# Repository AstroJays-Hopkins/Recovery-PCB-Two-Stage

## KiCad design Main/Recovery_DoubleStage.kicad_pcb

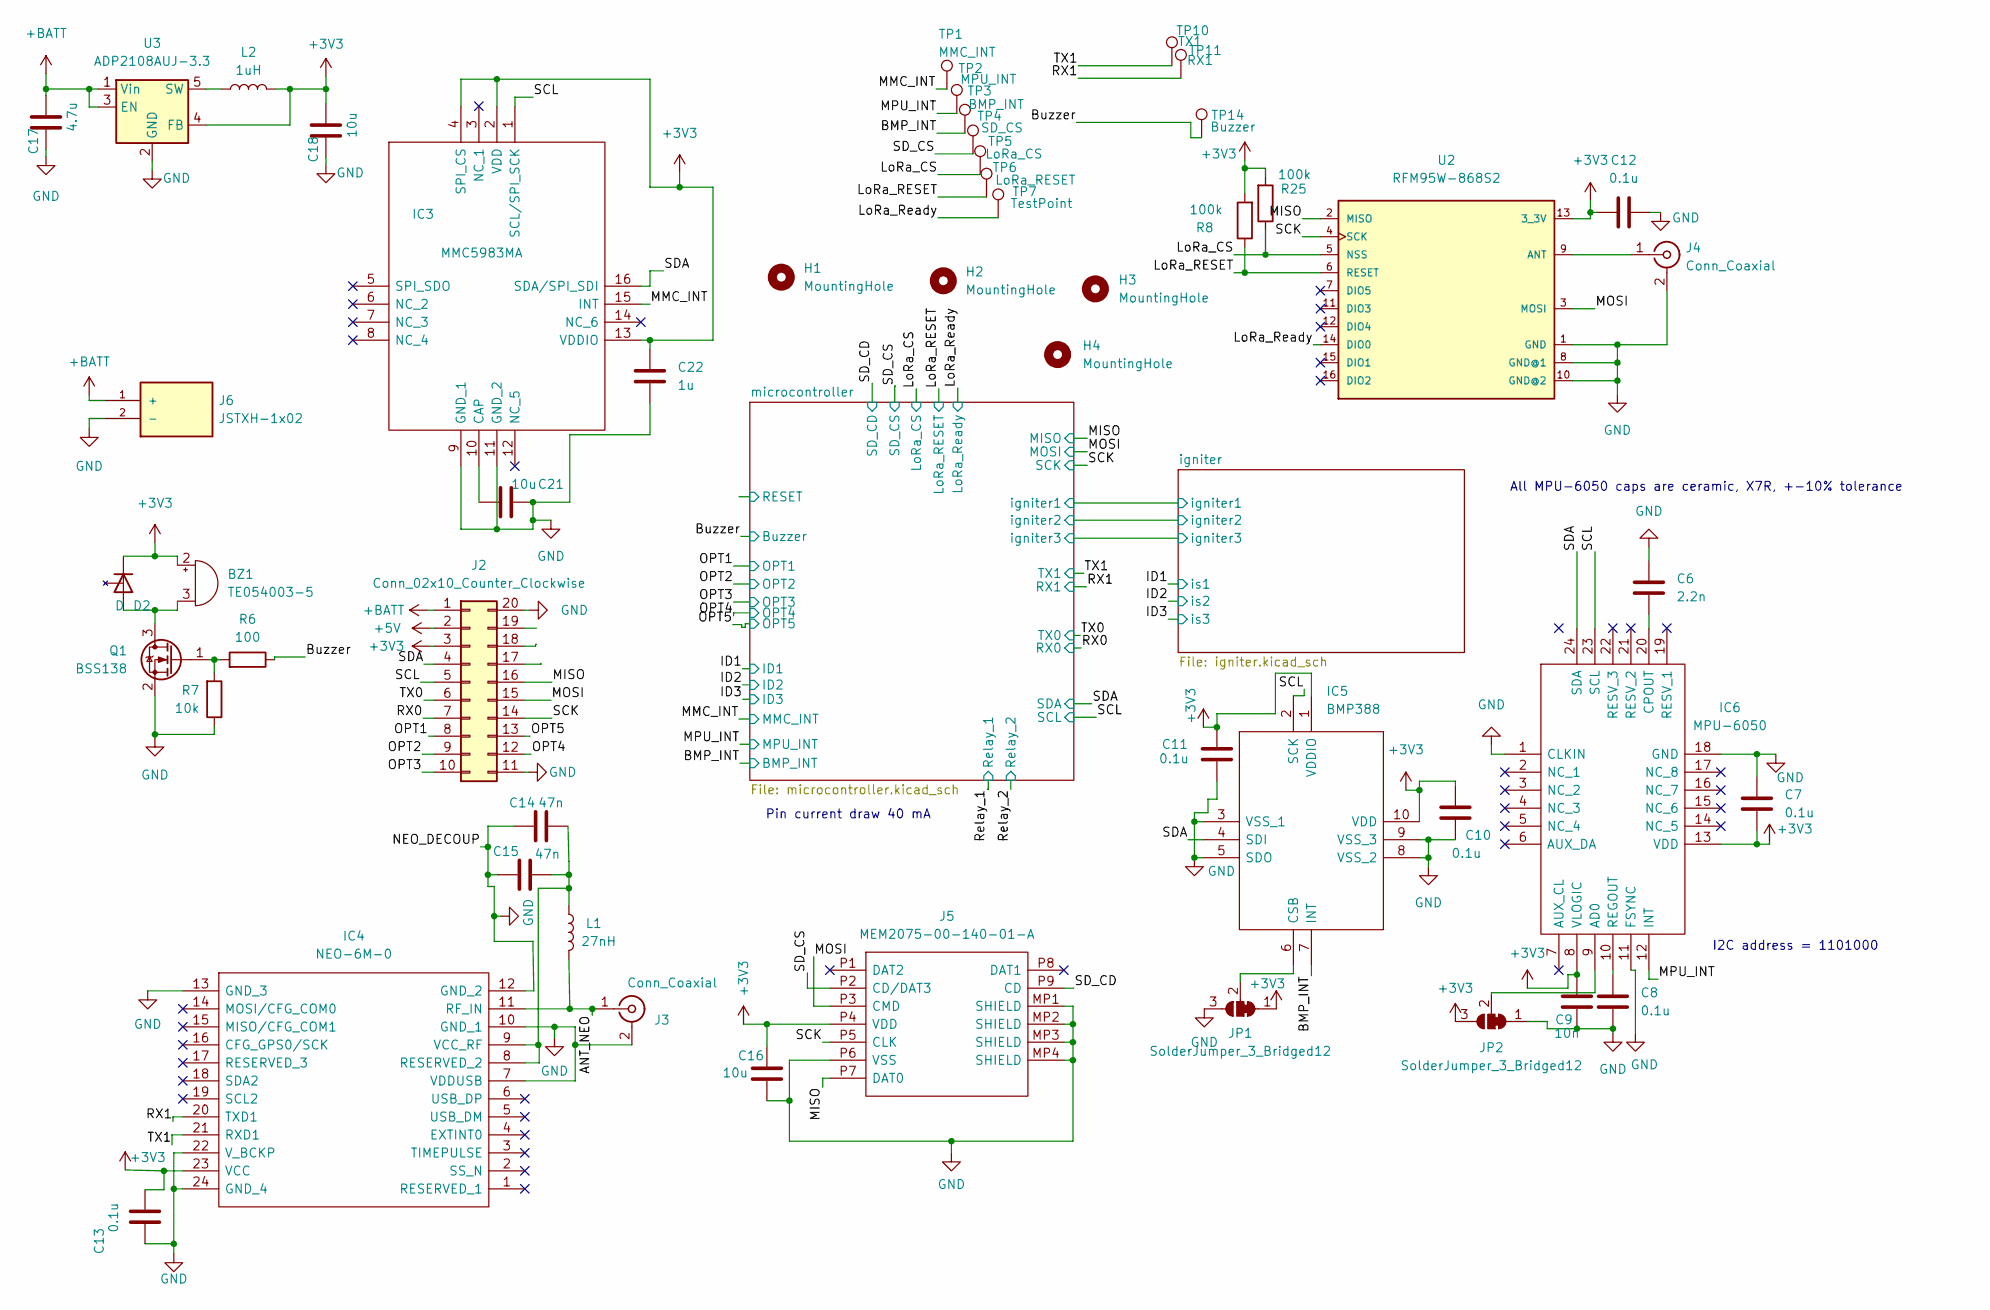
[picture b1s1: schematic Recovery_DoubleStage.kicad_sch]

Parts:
BZ1: TE054003-5; TE054003
C6: 2.2n; C_0603_1608Metric
C7, C8, C10, C11, C12, C13: 0.1u; C_0603_1608Metric
C9: 10n; C_0603_1608Metric
C14, C15: 47n; C_0603_1608Metric
C16, C18, C21: 10u; C_0603_1608Metric
C17: 4.7u; C_0603_1608Metric
C22: 1u; C_0603_1608Metric
D2: D; TSOT-23
H1, H2, H3, H4: MountingHole; MountingHole_3.2mm_M3
IC3: MMC5983MA; Manufacturer_Part_Number MMC5983MA; Mouser Part Number 438-MMC5983MA
IC4: NEO-6M-0; NEO6M0; Manufacturer_Part_Number NEO-6M-0; Mouser Part Number 377-NEO-6M-0
IC5: BMP388; Manufacturer_Part_Number BMP388; Mouser Part Number 262-BMP388
IC6: MPU-6050; MPU6050; Manufacturer_Part_Number MPU-6050; Mouser Part Number 410-MPU-6050
J2: Conn_02x10_Counter_Clockwise; PinHeader_2x10_P2.54mm_Vertical
J3, J4: Conn_Coaxial; RF_Solutions_Ltd.-CON-SMA-EDGE-S-MFG
J5: MEM2075-00-140-01-A; MEM20750014001A; Manufacturer_Part_Number MEM2075-00-140-01-A; Mouser Part Number 640-MEM20750014001A
J6: JSTXH-1x02; JST_XH_B2B-XH-AM_1x02_P2.50mm_Vertical; PARTREV V1.2
JP1, JP2: SolderJumper_3_Bridged12; SolderJumper-3_P1.3mm_Bridged12_Pad1.0x1.5mm_NumberLabels
L1: 27nH; L_0402_1005Metric
L2: 1uH; L_0805_2012Metric
Q1: BSS138; SOT-23
R6: 100; R_0603_1608Metric
R7: 10k; R_0603_1608Metric
R8, R25: 100k; R_0603_1608Metric
TP1: MMC_INT; TestPoint_Pad_D1.0mm
TP2: MPU_INT; TestPoint_Pad_D1.0mm
TP3: BMP_INT; TestPoint_Pad_D1.0mm
TP4: SD_CS; TestPoint_Pad_D1.0mm
TP5: LoRa_CS; TestPoint_Pad_D1.0mm
TP6: LoRa_RESET; TestPoint_Pad_D1.0mm
TP7: TestPoint; TestPoint_Pad_D1.0mm
TP10: TX1; TestPoint_Pad_D1.0mm
TP11: RX1; TestPoint_Pad_D1.0mm
TP14: Buzzer; TestPoint_Pad_D1.0mm
U2: RFM95W-868S2; XCVR_RFM95W-868S2
U3: ADP2108AUJ-3.3; TSOT-23-5

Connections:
+3V3: BZ1.2 (+), C7.2, C9.1, C10.1, C11.1, C12.1, C13.1, C16.1, C18.2, C22.1, D2.3 (K), IC3.2 (VDD), IC3.4 (SPI_CS), IC3.13 (VDDIO), IC4.23 (VCC), IC5.1 (VDDIO), IC5.10 (VDD), IC6.8 (VLOGIC), IC6.13 (VDD), J2.3, J5.P4 (VDD), JP1.1 (A), JP2.3 (B), L2.2, R8.2, R25.2, U2.13 (3_3V), U3.4 (FB); also elsewhere on the board
+5V: J2.2
+BATT: C17.2, J2.1, J6.1 (+), U3.1 (Vin), U3.3 (EN)
/ANT_NEO: IC4.11 (RF_IN), J3.1 (In), L1.2
/BMP_INT: IC5.7 (INT), TP3.1; also elsewhere on the board
/Buzzer: R6.1, TP14.1; also elsewhere on the board
/LoRa_CS: R25.1, TP5.1, U2.5 (NSS); also elsewhere on the board
/LoRa_RESET: R8.1, TP6.1, U2.6 (RESET); also elsewhere on the board
/LoRa_Ready: TP7.1, U2.14 (DIO0); also elsewhere on the board
/MISO: J2.16, J5.P7 (DAT0), U2.2 (MISO); also elsewhere on the board
/MMC_INT: IC3.15 (INT), TP1.1; also elsewhere on the board
/MOSI: J2.15, J5.P3 (CMD), U2.3 (MOSI); also elsewhere on the board
/MPU_INT: IC6.12 (INT), TP2.1; also elsewhere on the board
/OPT1: J2.8; also elsewhere on the board
/OPT2: J2.9; also elsewhere on the board
/OPT3: J2.10; also elsewhere on the board
/OPT4: J2.12; also elsewhere on the board
/OPT5: J2.13; also elsewhere on the board
/RX0: J2.7; also elsewhere on the board
/RX1: IC4.20 (TXD1), TP11.1; also elsewhere on the board
/SCK: J2.14, J5.P5 (CLK), U2.4 (SCK); also elsewhere on the board
/SCL: IC3.1 (SCL/SPI_SCK), IC5.2 (SCK), IC6.23 (SCL), J2.5; also elsewhere on the board
/SDA: IC3.16 (SDA/SPI_SDI), IC5.4 (SDI), IC6.24 (SDA), J2.4; also elsewhere on the board
/SD_CD: J5.P9 (CD); also elsewhere on the board
/SD_CS: J5.P2 (CD/DAT3), TP4.1; also elsewhere on the board
/TX0: J2.6; also elsewhere on the board
/TX1: IC4.21 (RXD1), TP10.1; also elsewhere on the board
GND: C6.1, C7.1, C8.2, C9.2, C10.2, C11.2, C12.2, C13.2, C14.1, C15.1, C16.2, C17.1, C18.1, C21.2, C22.2, IC3.9 (GND_1), IC3.11 (GND_2), IC4.7 (VDDUSB), IC4.10 (GND_1), IC4.12 (GND_2), IC4.13 (GND_3), IC4.22 (V_BCKP), IC4.24 (GND_4), IC5.3 (VSS_1), IC5.5 (SDO), IC5.8 (VSS_2), IC5.9 (VSS_3), IC6.1 (CLKIN), IC6.11 (FSYNC), IC6.18 (GND), J2.11, J2.20, J3.2 (Ext), J4.2 (Ext), J5.MP1 (SHIELD), J5.MP2 (SHIELD), J5.MP3 (SHIELD), J5.MP4 (SHIELD), J5.P6 (VSS), J6.2 (-), JP1.3 (B), JP2.1 (A), Q1.2 (S), R7.1, U2.1 (GND), U2.8 (GND@1), U2.10 (GND@2), U3.2 (GND); also elsewhere on the board
unnamed: BZ1.3 (+), D2.1 (A), Q1.3 (D)
unnamed: C6.2, IC6.20 (CPOUT)
unnamed: C8.1, IC6.10 (REGOUT)
unnamed: C14.2, C15.2, IC4.8 (RESERVED_2), IC4.9 (VCC_RF), L1.1
unnamed: C21.1, IC3.10 (CAP)
unnamed: IC5.6 (CSB), JP1.2 (C)
unnamed: IC6.9 (AD0), JP2.2 (C)
unnamed: J4.1 (In), U2.9 (ANT)
unnamed: L2.1, U3.5 (SW)
unnamed: Q1.1 (G), R6.2, R7.2

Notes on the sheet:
I2C address = 1101000
All MPU-6050 caps are ceramic, X7R, +-10% tolerance
Pin current draw 40 mA

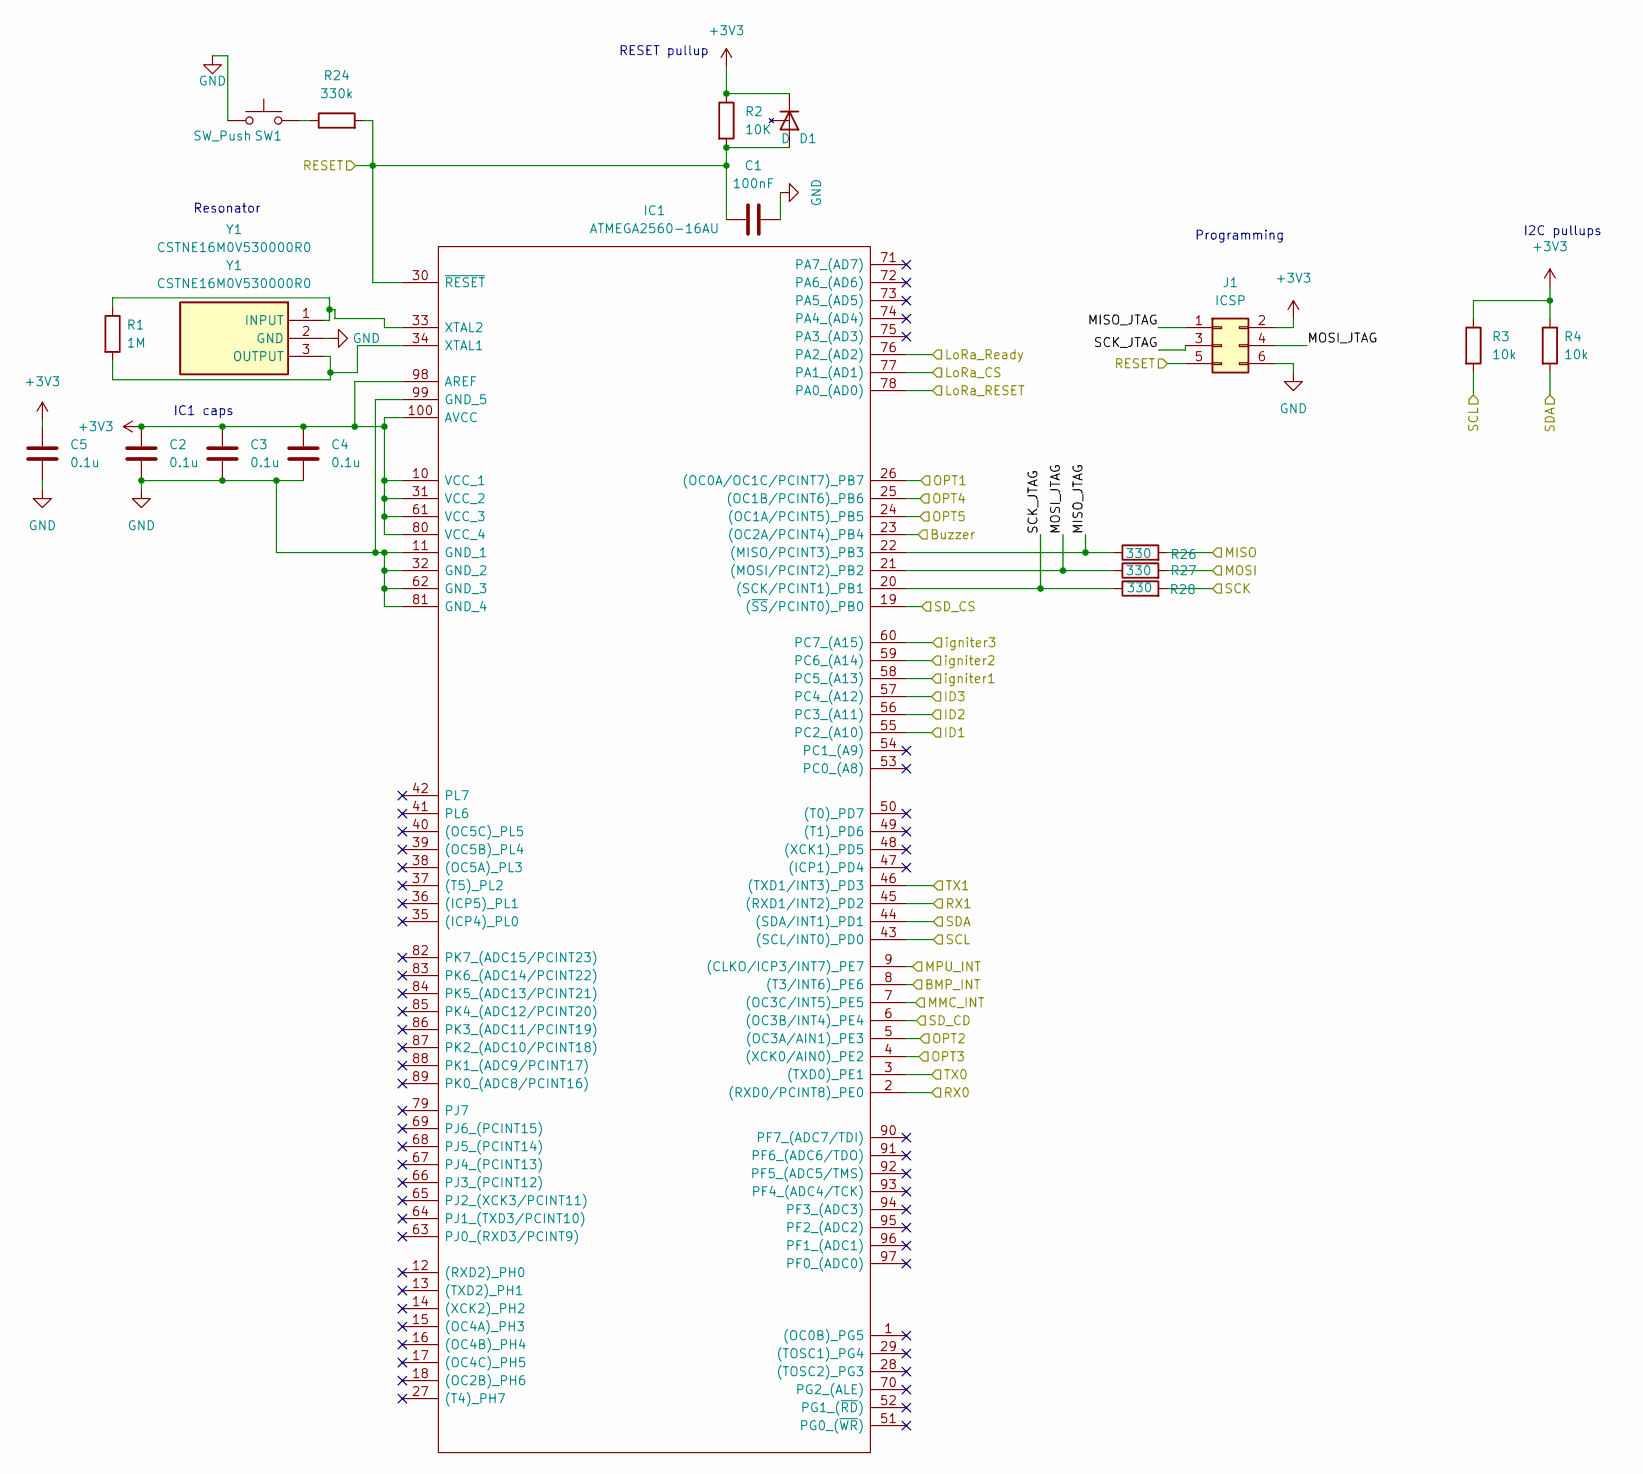
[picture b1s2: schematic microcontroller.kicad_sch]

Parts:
C1: 100nF; C_0603_1608Metric
C2, C3, C4, C5: 0.1u; C_0603_1608Metric
D1: D; TSOT-23
IC1: ATMEGA2560-16AU; QFP50P1600X1600X120-100N; Manufacturer_Part_Number ATMEGA2560-16AU; Mouser Part Number 556-ATMEGA2560-16AU
J1: ICSP; PinHeader_2x03_P2.54mm_Vertical
R1: 1M; R_0603_1608Metric
R2: 10K; R_0603_1608Metric
R3, R4: 10k; R_0603_1608Metric
R24: 330k; R_0603_1608Metric
R26, R27, R28: 330; R_0603_1608Metric
SW1: SW_Push; PTS815SJK250SMTRLFS
Y1: CSTNE16M0V530000R0; Manufacturer_Part_Number CSTNE16M0V530000R0; Mouser Part Number 81-CSTNE16M0V530000R

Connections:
+3V3: C2.1, C3.1, C4.1, C5.1, D1.3 (K), IC1.10 (VCC_1), IC1.31 (VCC_2), IC1.61 (VCC_3), IC1.80 (VCC_4), IC1.98 (AREF), IC1.100 (AVCC), J1.2, R2.1, R3.1, R4.1; also elsewhere on the board
/BMP_INT: IC1.8 ((T3/INT6)_PE6); also elsewhere on the board
/Buzzer: IC1.23 ((OC2A/PCINT4)_PB4); also elsewhere on the board
/ID1: IC1.55 (PC2_(A10)); also elsewhere on the board
/ID2: IC1.56 (PC3_(A11)); also elsewhere on the board
/ID3: IC1.57 (PC4_(A12)); also elsewhere on the board
/LoRa_CS: IC1.77 (PA1_(AD1)); also elsewhere on the board
/LoRa_RESET: IC1.78 (PA0_(AD0)); also elsewhere on the board
/LoRa_Ready: IC1.76 (PA2_(AD2)); also elsewhere on the board
/MISO: R26.2; also elsewhere on the board
/MMC_INT: IC1.7 ((OC3C/INT5)_PE5); also elsewhere on the board
/MOSI: R27.2; also elsewhere on the board
/MPU_INT: IC1.9 ((CLKO/ICP3/INT7)_PE7); also elsewhere on the board
/OPT1: IC1.26 ((OC0A/OC1C/PCINT7)_PB7); also elsewhere on the board
/OPT2: IC1.5 ((OC3A/AIN1)_PE3); also elsewhere on the board
/OPT3: IC1.4 ((XCK0/AIN0)_PE2); also elsewhere on the board
/OPT4: IC1.25 ((OC1B/PCINT6)_PB6); also elsewhere on the board
/OPT5: IC1.24 ((OC1A/PCINT5)_PB5); also elsewhere on the board
/RX0: IC1.2 ((RXD0/PCINT8)_PE0); also elsewhere on the board
/RX1: IC1.45 ((RXD1/INT2)_PD2); also elsewhere on the board
/SCK: R28.2; also elsewhere on the board
/SCL: IC1.43 ((SCL/INT0)_PD0), R3.2; also elsewhere on the board
/SDA: IC1.44 ((SDA/INT1)_PD1), R4.2; also elsewhere on the board
/SD_CD: IC1.6 ((OC3B/INT4)_PE4); also elsewhere on the board
/SD_CS: IC1.19 ((~SS/PCINT0)_PB0); also elsewhere on the board
/TX0: IC1.3 ((TXD0)_PE1); also elsewhere on the board
/TX1: IC1.46 ((TXD1/INT3)_PD3); also elsewhere on the board
/igniter/igniter1: IC1.58 (PC5_(A13)); also elsewhere on the board
/igniter/igniter2: IC1.59 (PC6_(A14)); also elsewhere on the board
/igniter/igniter3: IC1.60 (PC7_(A15)); also elsewhere on the board
/microcontroller/MISO_JTAG: IC1.22 ((MISO/PCINT3)_PB3), J1.1, R26.1
/microcontroller/MOSI_JTAG: IC1.21 ((MOSI/PCINT2)_PB2), J1.4, R27.1
/microcontroller/RESET: C1.1, D1.1 (A), IC1.30 (~RESET), J1.5, R2.2, R24.2
/microcontroller/SCK_JTAG: IC1.20 ((SCK/PCINT1)_PB1), J1.3, R28.1
GND: C1.2, C2.2, C3.2, C4.2, C5.2, IC1.11 (GND_1), IC1.32 (GND_2), IC1.62 (GND_3), IC1.81 (GND_4), IC1.99 (GND_5), J1.6, SW1.1, Y1.2 (GND); also elsewhere on the board
unnamed: IC1.33 (XTAL2), R1.1, Y1.1 (INPUT)
unnamed: IC1.34 (XTAL1), R1.2, Y1.3 (OUTPUT)
unnamed: R24.1, SW1.2

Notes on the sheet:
IC1 caps
Resonator
Programming
I2C pullups
RESET pullup

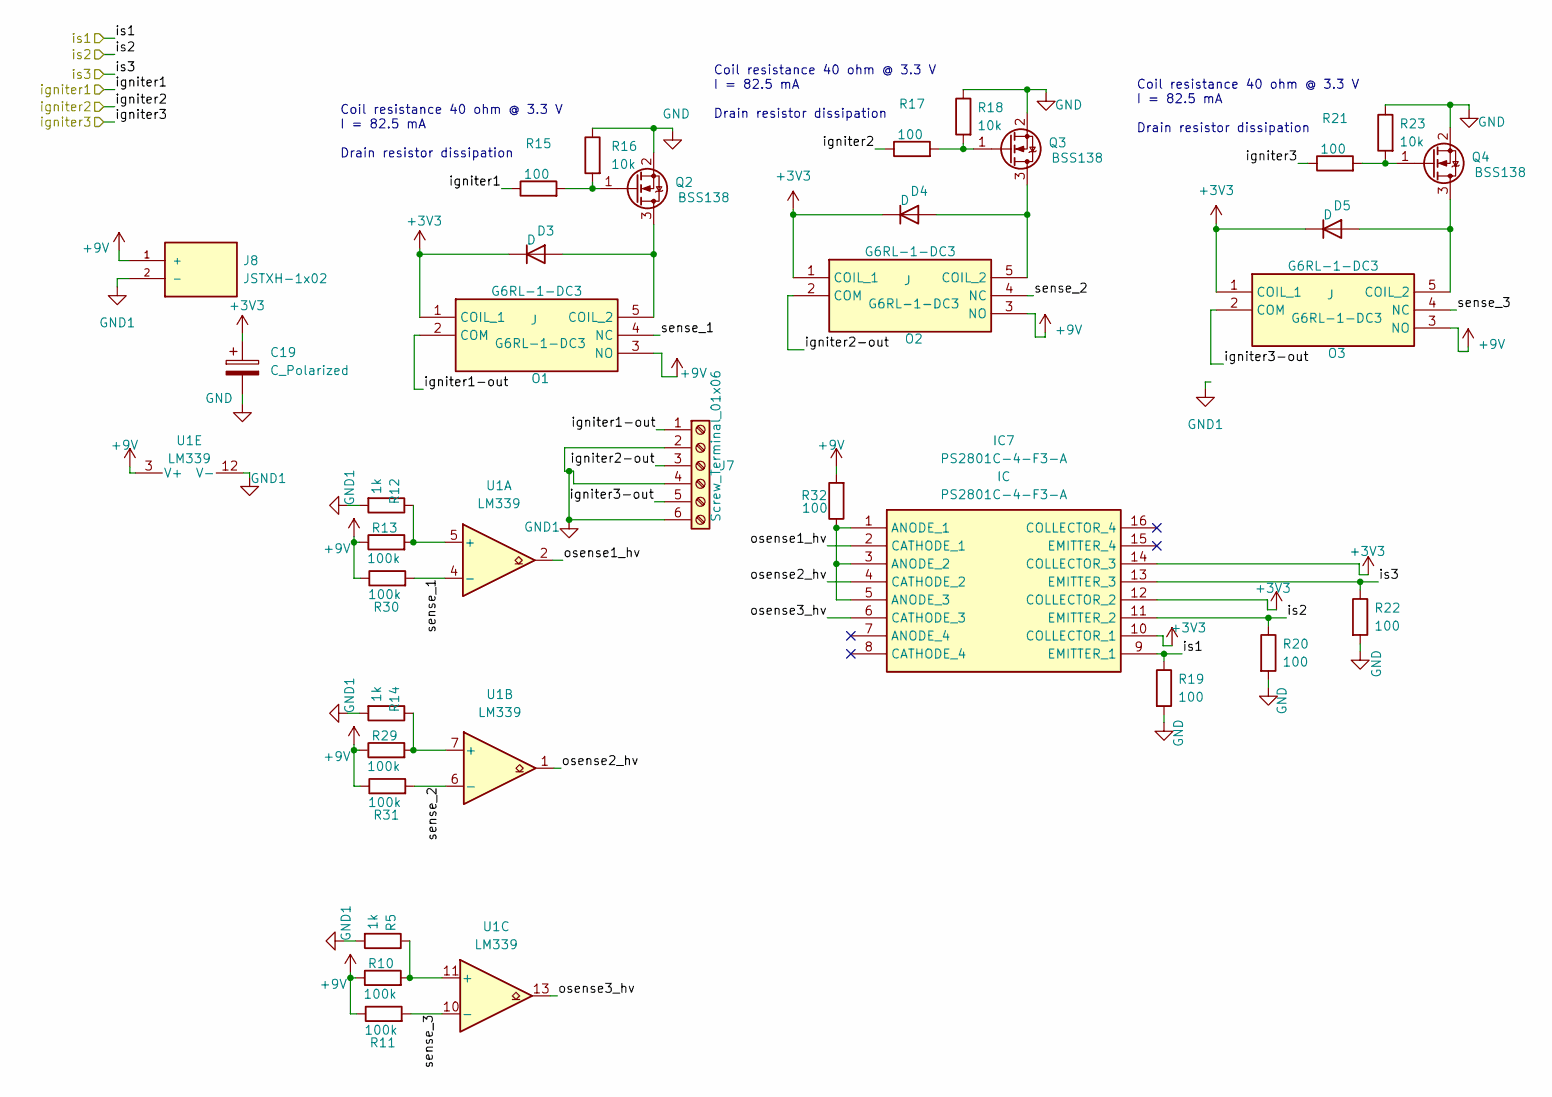
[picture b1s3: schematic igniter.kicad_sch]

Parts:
C19: C_Polarized; CP_Elec_6.3x7.7
D3, D4, D5: D; TSOT-23
IC7: PS2801C-4-F3-A; SOIC127P700X230-16N; Manufacturer_Part_Number PS2801C-4-F3-A; Mouser Part Number 968-PS2801C-4-F3-A
J7: Screw_Terminal_01x06; TerminalBlock_bornier-6_P5.08mm
J8: JSTXH-1x02; JST_XH_B2B-XH-AM_1x02_P2.50mm_Vertical; PARTREV V1.2
O1, O2, O3: G6RL-1-DC3; G6RL1DC5; Manufacturer_Part_Number G6RL-1-DC3; Mouser Part Number 653-G6RL-1-DC3
Q2, Q3, Q4: BSS138; SOT-23
R5, R12, R14: 1k; R_0603_1608Metric
R10, R11, R13, R29, R30, R31: 100k; R_0603_1608Metric
R15, R17, R19, R20, R21, R22, R32: 100; R_0603_1608Metric
R16, R18, R23: 10k; R_0603_1608Metric
U1: LM339; TSSOP-14_4.4x5mm_P0.65mm

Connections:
+3V3: C19.1, D3.1 (K), D4.1 (K), D5.1 (K), IC7.10 (COLLECTOR_1), IC7.12 (COLLECTOR_2), IC7.14 (COLLECTOR_3), O1.1 (COIL_1), O2.1 (COIL_1), O3.1 (COIL_1); also elsewhere on the board
+9V: J8.1 (+), O1.3 (NO), O2.3 (NO), O3.3 (NO), R10.1, R11.1, R13.1, R29.1, R30.1, R31.1, R32.2, U1.3 (V+)
/ID1: IC7.9 (EMITTER_1), R19.1; also elsewhere on the board
/ID2: IC7.11 (EMITTER_2), R20.1; also elsewhere on the board
/ID3: IC7.13 (EMITTER_3), R22.1; also elsewhere on the board
/igniter/igniter1: R15.1; also elsewhere on the board
/igniter/igniter1-out: J7.1, O1.2 (COM)
/igniter/igniter2: R17.1; also elsewhere on the board
/igniter/igniter2-out: J7.3, O2.2 (COM)
/igniter/igniter3: R21.1; also elsewhere on the board
/igniter/igniter3-out: J7.5, O3.2 (COM)
/igniter/osense1_hv: IC7.2 (CATHODE_1), U1.2
/igniter/osense2_hv: IC7.4 (CATHODE_2), U1.1
/igniter/osense3_hv: IC7.6 (CATHODE_3), U1.13
/igniter/sense_1: O1.4 (NC), R30.2, U1.4 (-)
/igniter/sense_2: O2.4 (NC), R31.2, U1.6 (-)
/igniter/sense_3: O3.4 (NC), R11.2, U1.10 (-)
GND: C19.2, Q2.2 (S), Q3.2 (S), Q4.2 (S), R16.1, R18.1, R19.2, R20.2, R22.2, R23.1; also elsewhere on the board
GND1: J7.2, J7.4, J7.6, J8.2 (-), R5.2, R12.2, R14.2, U1.12 (V-)
unnamed: D3.2 (A), O1.5 (COIL_2), Q2.3 (D)
unnamed: D4.2 (A), O2.5 (COIL_2), Q3.3 (D)
unnamed: D5.2 (A), O3.5 (COIL_2), Q4.3 (D)
unnamed: IC7.1 (ANODE_1), IC7.3 (ANODE_2), IC7.5 (ANODE_3), R32.1
unnamed: Q2.1 (G), R15.2, R16.2
unnamed: Q3.1 (G), R17.2, R18.2
unnamed: Q4.1 (G), R21.2, R23.2
unnamed: R5.1, R10.2, U1.11 (+)
unnamed: R12.1, R13.2, U1.5 (+)
unnamed: R14.1, R29.2, U1.7 (+)

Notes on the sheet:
Coil resistance 40 ohm @ 3.3 V I = 82.5 mA Drain resistor dissipation

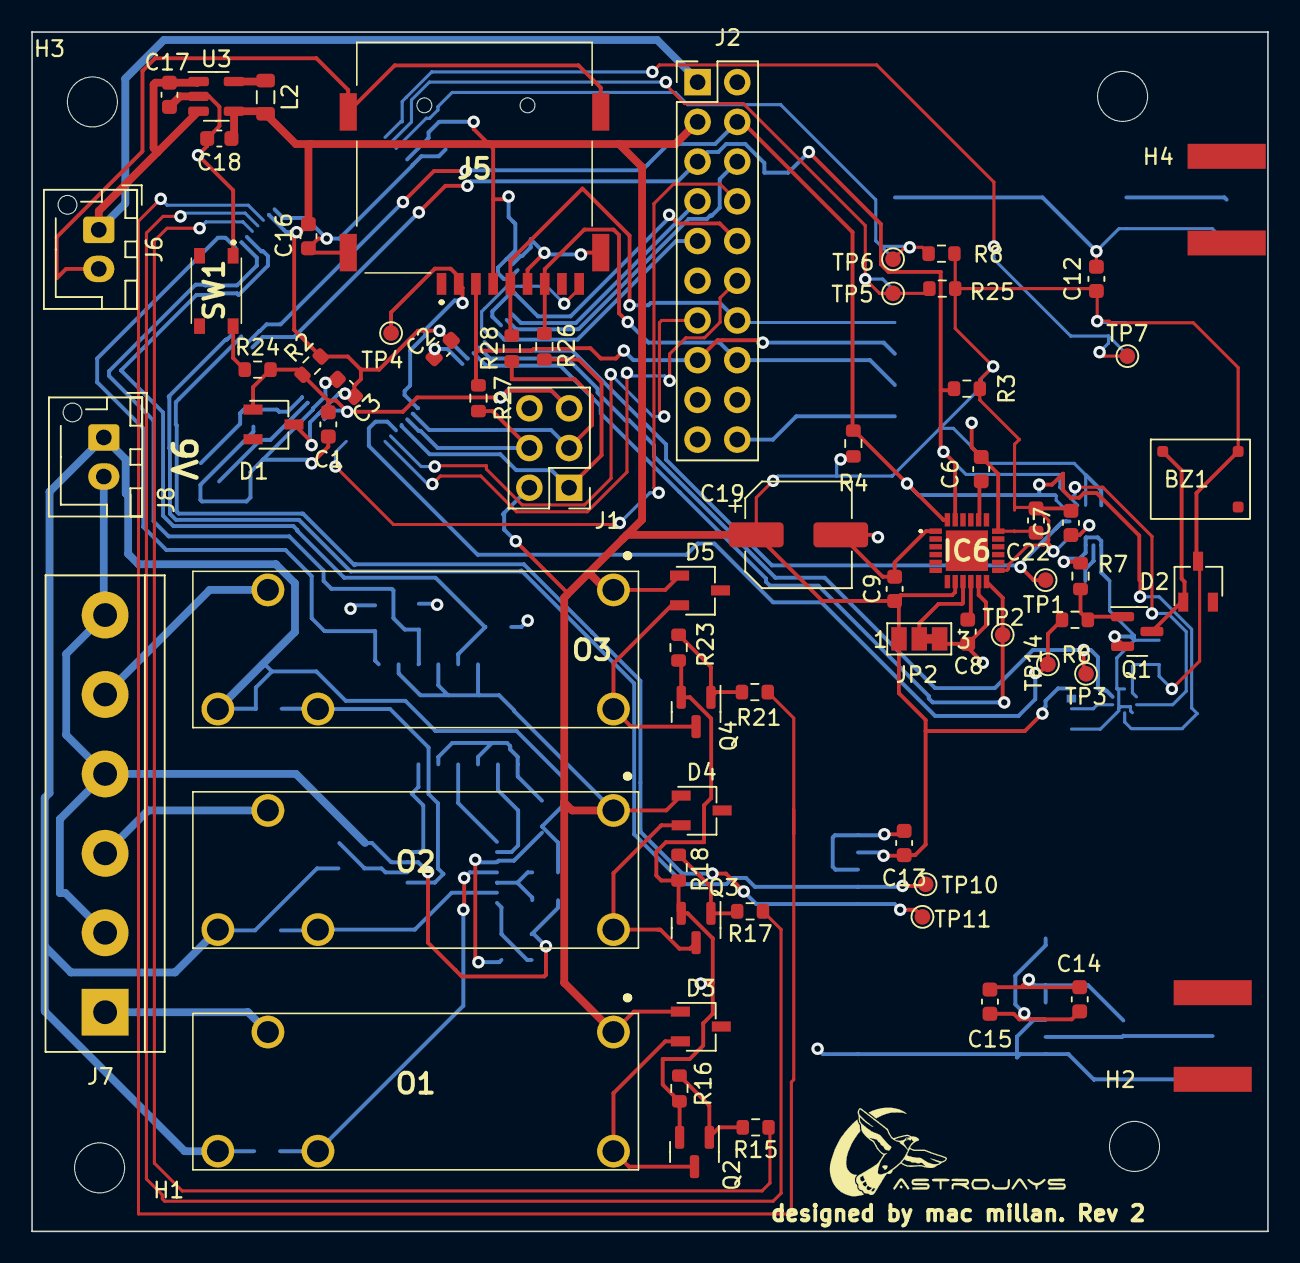
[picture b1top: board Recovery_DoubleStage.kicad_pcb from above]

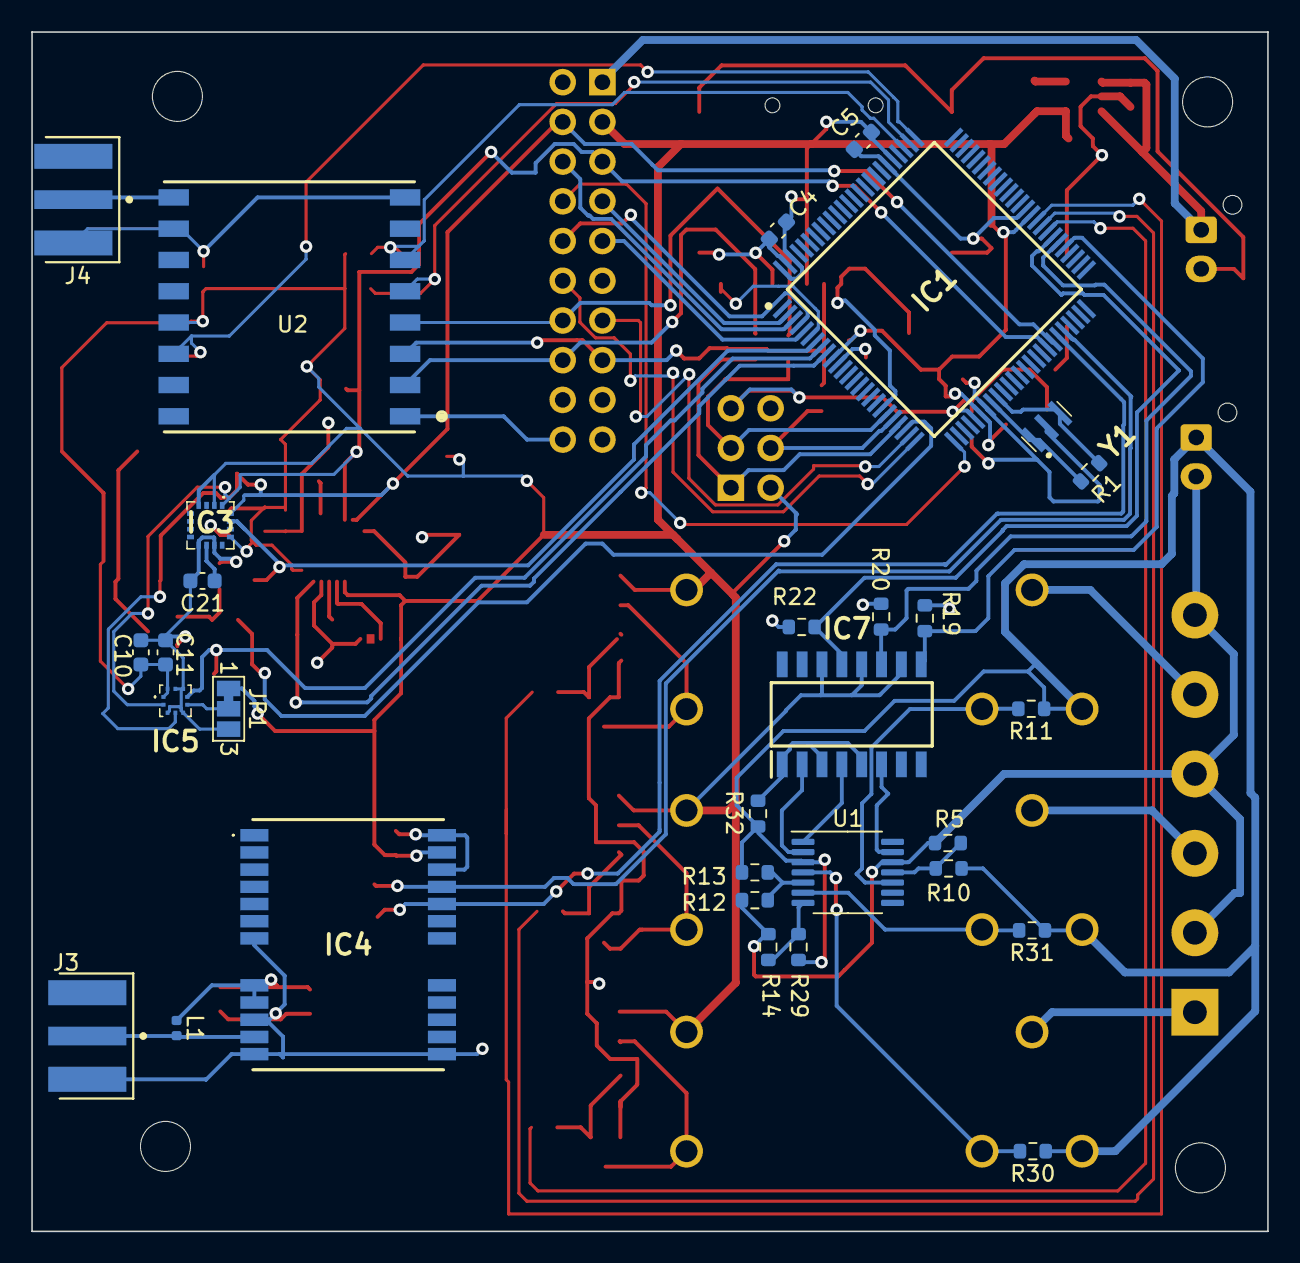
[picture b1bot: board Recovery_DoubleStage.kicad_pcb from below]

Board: 4 copper layers, 79.0 x 76.7 mm, 102 parts (31 on the bottom side), 71 nets.

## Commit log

2023-02-03 added symbol for atmega2560
2023-02-08 finished microcontroller schematic. started laying out LoRa and IMU
2023-02-08 forgot to add project and schematic changes
2023-02-09 atmega2560 at 3v3 now. almost done with SD card
2023-02-10 did power rails, gps, and SD card, and altimiter.
2023-02-12 updating schematic
2023-02-12 added ignition detection circuit
2023-04-14 restructured schematic and just started routing
2023-04-16 almost done with routing
2023-10-15 reworking
2023-10-15 added relative paths
2023-10-15 reviewed design. starting routing
2023-11-27 finalized pcb
2023-11-28 added full schematic plot
2024-02-16 latest PCB version with BOM
